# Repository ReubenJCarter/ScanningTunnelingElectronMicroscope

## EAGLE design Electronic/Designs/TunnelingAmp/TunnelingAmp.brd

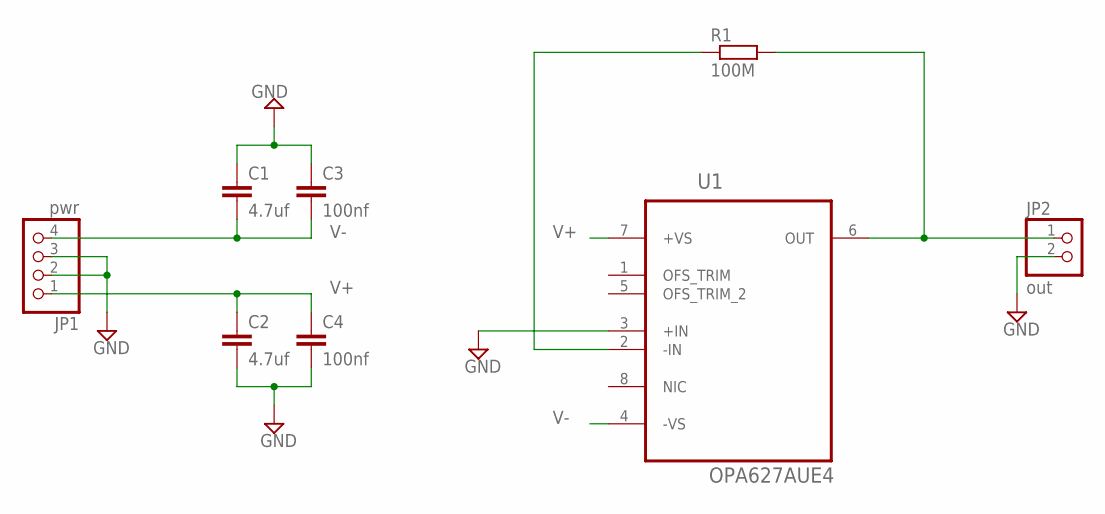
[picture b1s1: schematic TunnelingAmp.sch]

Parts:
C1, C2: 4.7uf; C1210
C3, C4: 100nf; C0603
JP1: pwr; 1X04
JP2: out; 1X02
R1: 100M; R0805
U1: OPA627AUE4; SOIC127P600X175-8N

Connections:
GND: C1.1, C2.2, C3.1, C4.2, JP1.2, JP1.3, JP2.2, U1.3 (+IN)
unnamed: R1.1, U1.2 (-IN)
unnamed: JP2.1, R1.2, U1.6 (OUT)
V+: C2.1, C4.1, JP1.1, U1.7 (+VS)
V-: C1.2, C3.2, JP1.4, U1.4 (-VS)

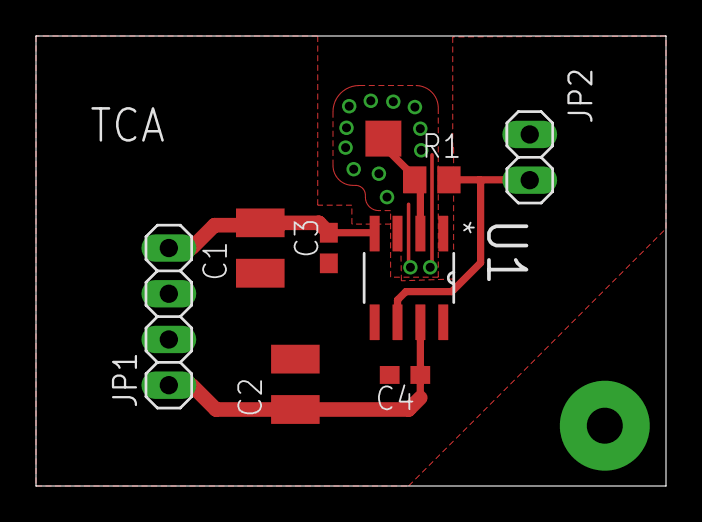
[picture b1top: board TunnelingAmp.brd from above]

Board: 2 copper layers, 35.0 x 25.0 mm, 8 parts (0 on the bottom side), 5 nets.

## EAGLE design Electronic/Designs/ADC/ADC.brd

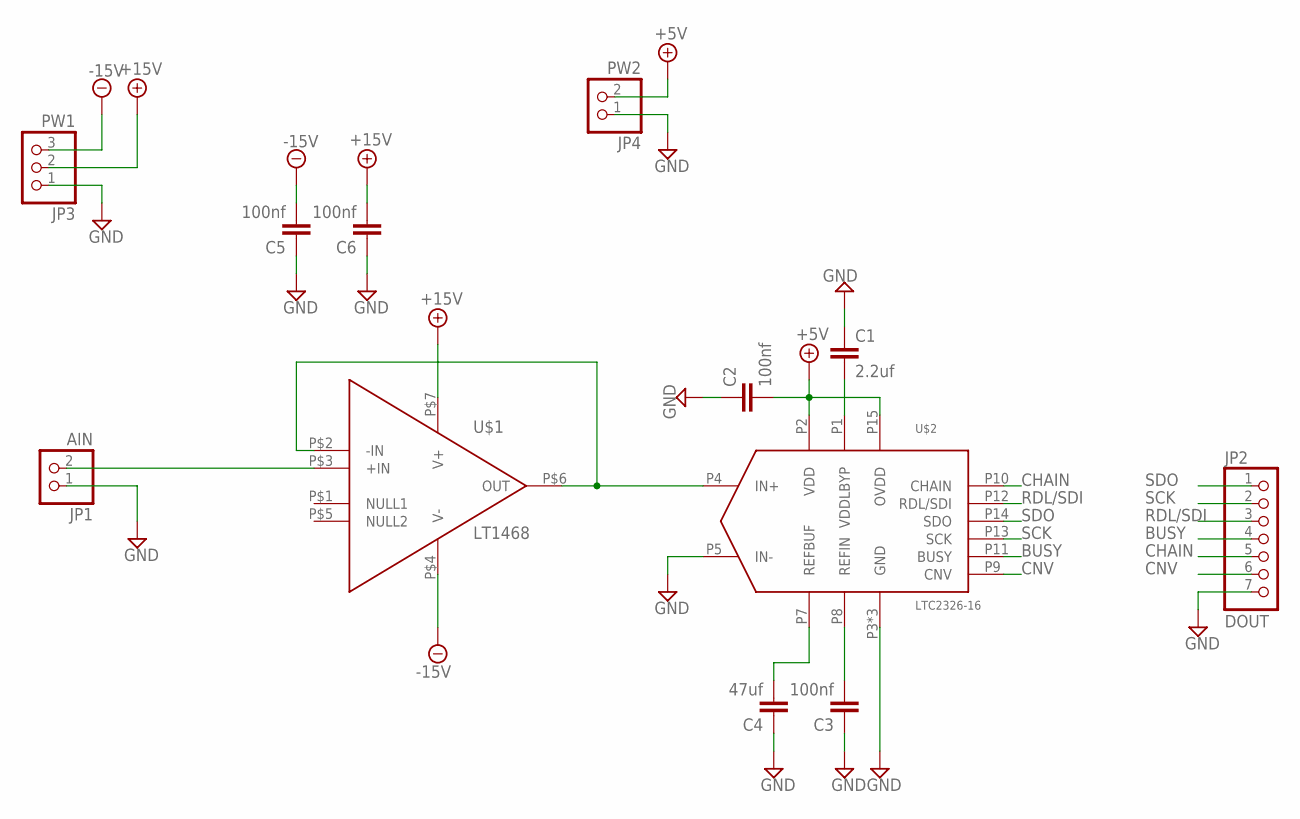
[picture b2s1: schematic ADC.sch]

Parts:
C1: 2.2uf; C0603
C2, C3, C5, C6: 100nf; C0603
C4: 47uf; C0603
JP1: AIN; 1X02
JP2: DOUT; 1X07
JP3: PW1; 1X03
JP4: PW2; 1X02
U$1: LT1468; SOIC-8
U$2: LTC2326-16; 16-MSOP

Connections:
+5V: C2.2, JP4.2, U$2.P2 (VDD), U$2.P15 (OVDD)
+15V: C6.2, JP3.2, U$1.P$7 (V+)
-15V: C5.2, JP3.3, U$1.P$4 (V-)
BUSY: JP2.4, U$2.P11 (BUSY)
CHAIN: JP2.5, U$2.P10 (CHAIN)
CNV: JP2.6, U$2.P9 (CNV)
GND: C1.1, C2.1, C3.1, C4.1, C5.1, C6.1, JP1.1, JP2.7, JP3.1, JP4.1, U$2.P3 (GND), U$2.P5 (IN-), U$2.P6 (GND), U$2.P16 (GND)
unnamed: U$1.P$2 (-IN), U$1.P$6 (OUT), U$2.P4 (IN+)
unnamed: C4.2, U$2.P7 (REFBUF)
unnamed: C3.2, U$2.P8 (REFIN)
unnamed: C1.2, U$2.P1 (VDDLBYP)
unnamed: JP1.2, U$1.P$3 (+IN)
RDL/SDI: JP2.3, U$2.P12 (RDL/SDI)
SCK: JP2.2, U$2.P13 (SCK)
SDO: JP2.1, U$2.P14 (SDO)

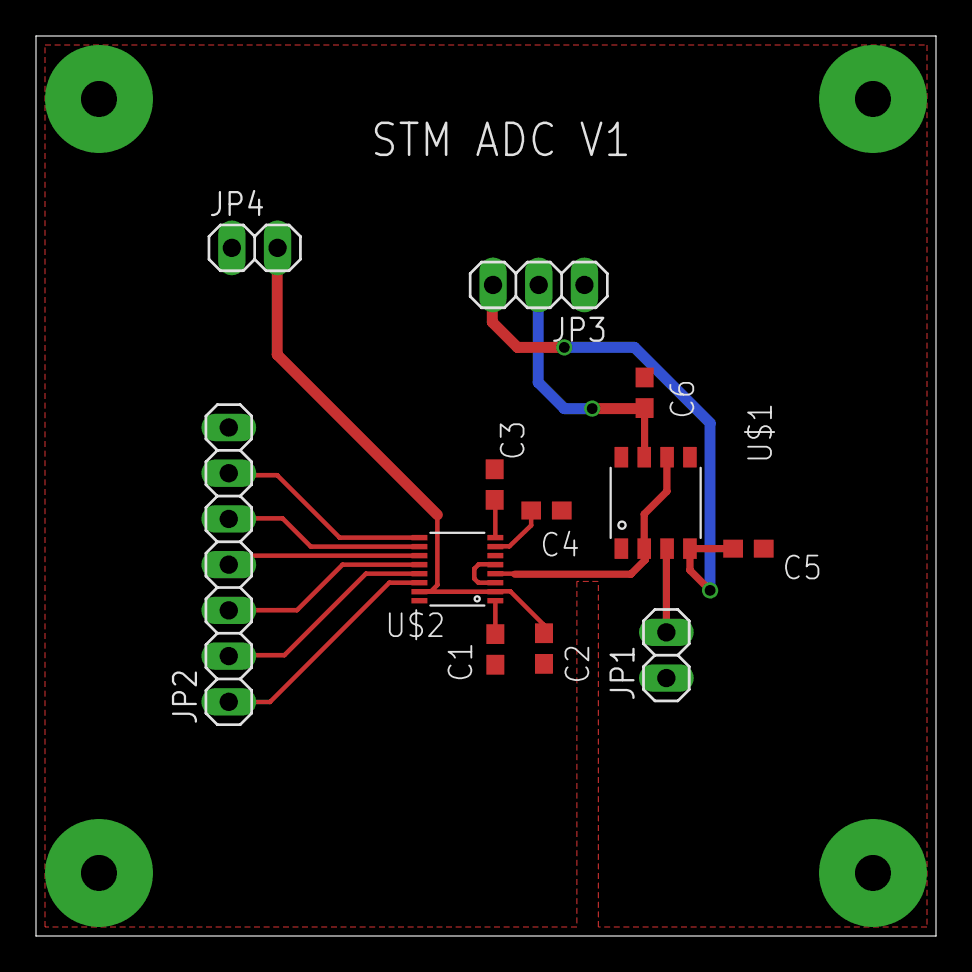
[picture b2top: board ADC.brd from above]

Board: 2 copper layers, 50.0 x 50.0 mm, 12 parts (0 on the bottom side), 15 nets.

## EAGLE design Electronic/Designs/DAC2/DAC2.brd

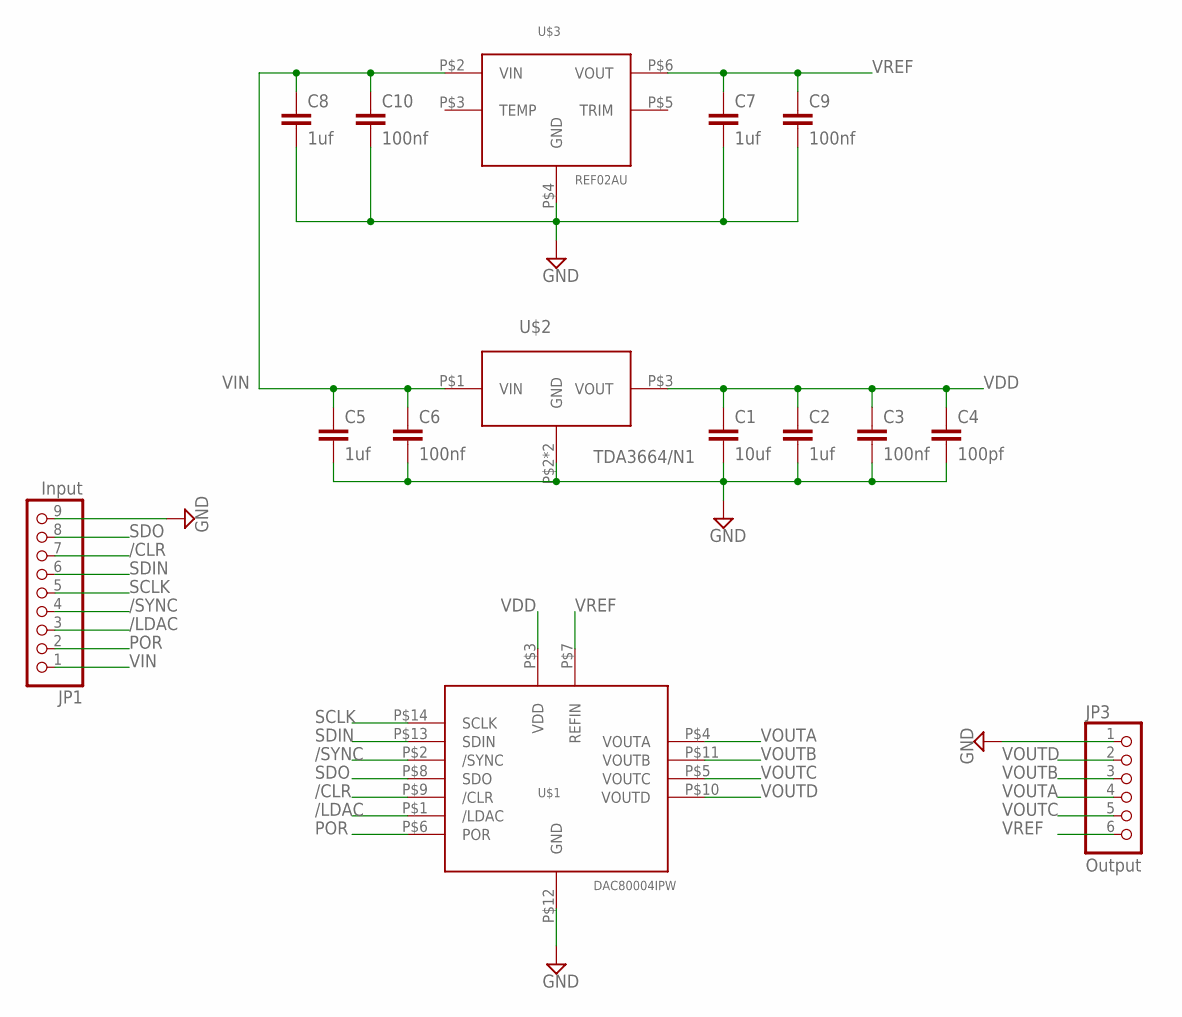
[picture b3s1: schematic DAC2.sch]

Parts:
C1: 10uf; C1210
C2, C5, C7, C8: 1uf; C0603
C3, C6, C9, C10: 100nf; C0603
C4: 100pf; C0603
JP1: Input; 1X09
JP3: Output; 1X06
U$1: DAC80004IPW; TSSOP14
U$2: TDA3664/N1; SOT223
U$3: REF02AU; SO8

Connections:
/CLR: JP1.7, U$1.P$9 (/CLR)
/LDAC: JP1.3, U$1.P$1 (/LDAC)
/SYNC: JP1.4, U$1.P$2 (/SYNC)
GND: C1.2, C2.2, C3.2, C4.2, C5.2, C6.2, C7.2, C8.2, C9.2, C10.2, JP1.9, JP3.1, U$1.P$12 (GND), U$2.P$2 (GND), U$2.P$4 (GND), U$3.P$4 (GND)
POR: JP1.2, U$1.P$6 (POR)
SCLK: JP1.5, U$1.P$14 (SCLK)
SDIN: JP1.6, U$1.P$13 (SDIN)
SDO: JP1.8, U$1.P$8 (SDO)
VDD: C1.1, C2.1, C3.1, C4.1, U$1.P$3 (VDD), U$2.P$3 (VOUT)
VIN: C5.1, C6.1, C8.1, C10.1, JP1.1, U$2.P$1 (VIN), U$3.P$2 (VIN)
VOUTA: JP3.4, U$1.P$4 (VOUTA)
VOUTB: JP3.3, U$1.P$11 (VOUTB)
VOUTC: JP3.5, U$1.P$5 (VOUTC)
VOUTD: JP3.2, U$1.P$10 (VOUTD)
VREF: C7.1, C9.1, JP3.6, U$1.P$7 (REFIN), U$3.P$6 (VOUT)

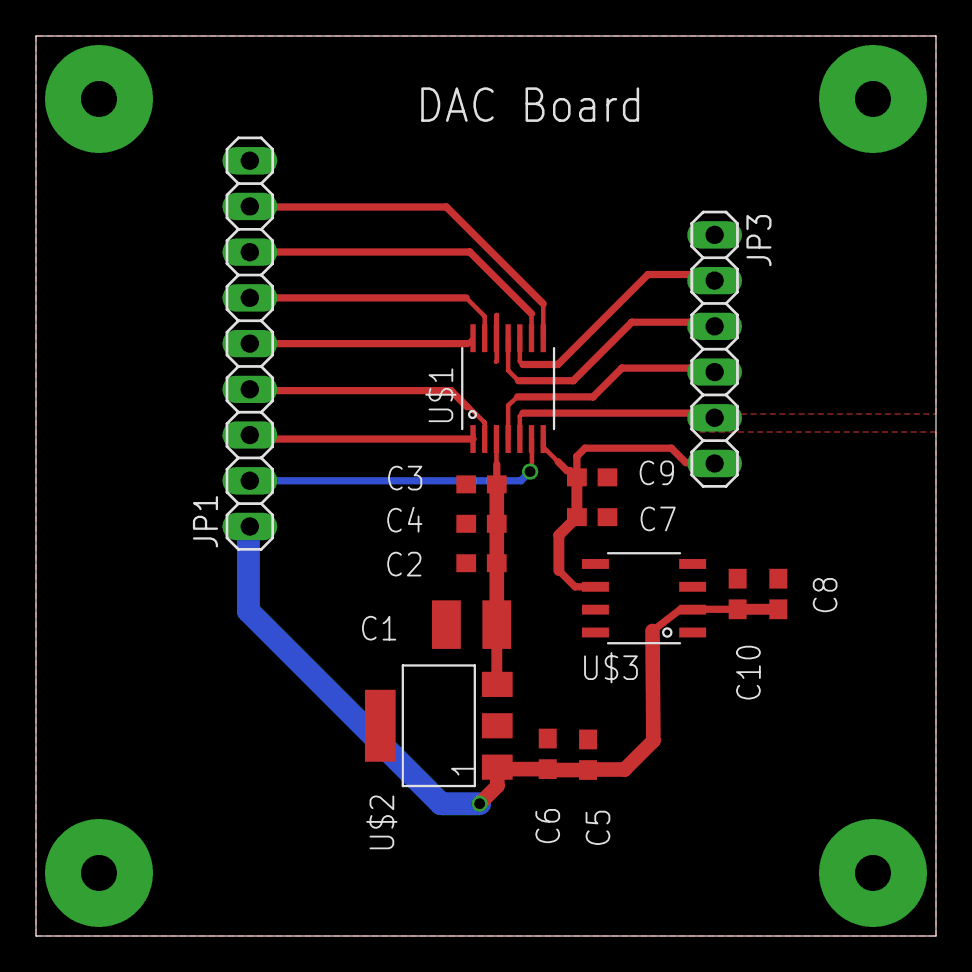
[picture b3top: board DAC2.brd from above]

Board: 2 copper layers, 50.0 x 50.0 mm, 15 parts (0 on the bottom side), 15 nets.

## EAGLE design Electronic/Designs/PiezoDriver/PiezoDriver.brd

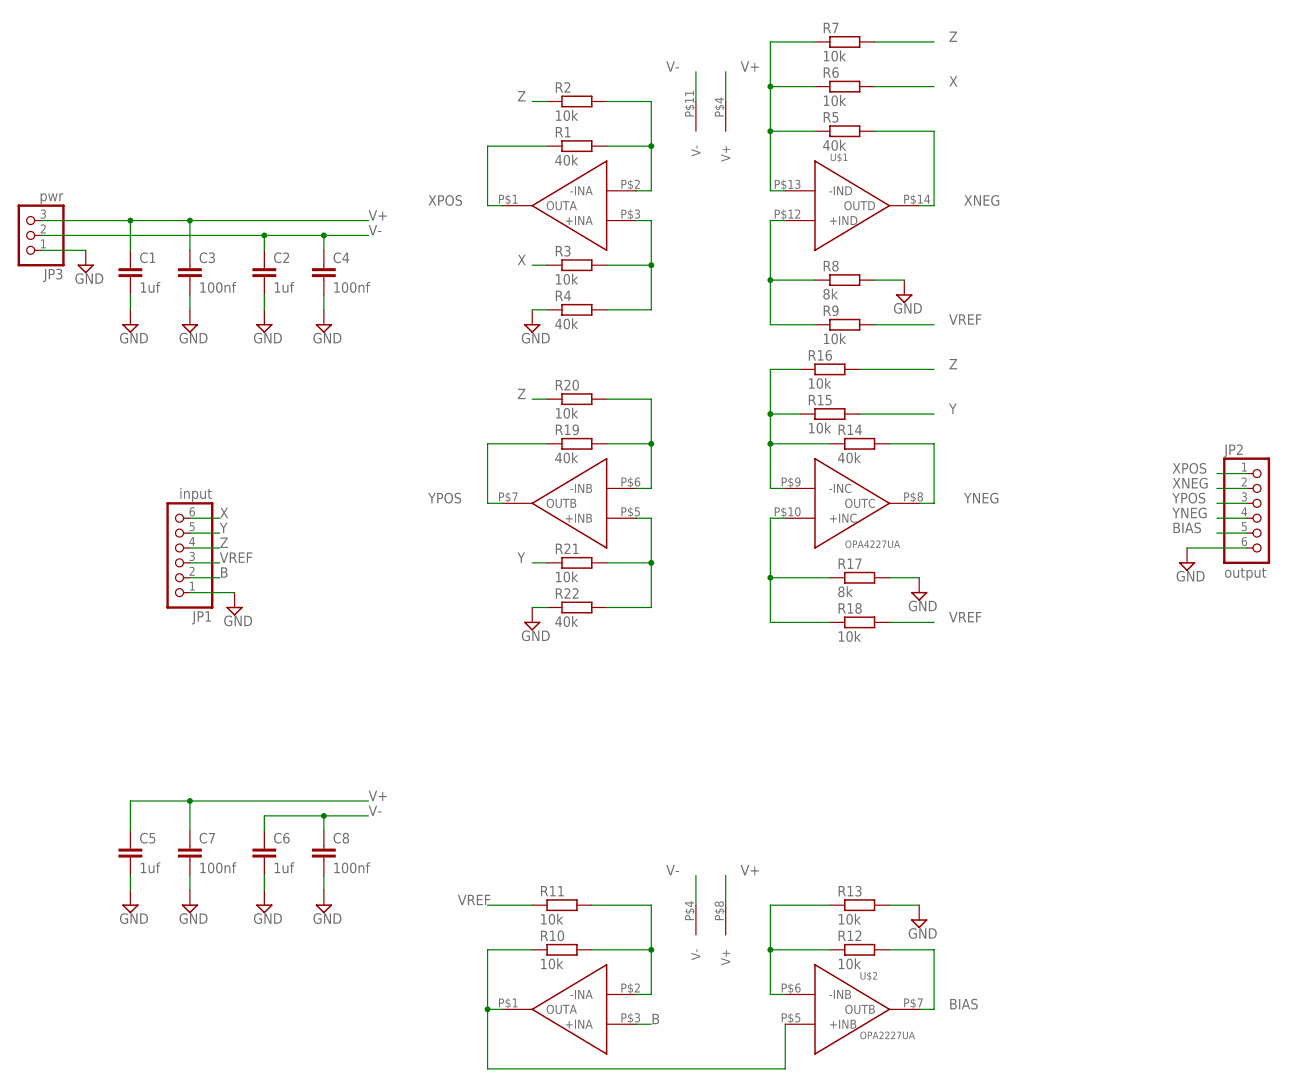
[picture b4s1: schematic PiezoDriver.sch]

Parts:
C1, C2, C5, C6: 1uf; C0603
C3, C4, C7, C8: 100nf; C0603
JP1: input; 1X06
JP2: output; 1X06
JP3: pwr; 1X03
R1, R4, R5, R14, R19, R22: 40k; R0603
R2, R3, R6, R7, R9, R10, R11, R12, R13, R15, R16, R18, R20, R21: 10k; R0603
R8, R17: 8k; R0603
U$1: OPA4227UA; SOIC-14
U$2: OPA2227UA; SOIC-8

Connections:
B: JP1.2, U$2.P$3 (+INA)
BIAS: JP2.5, R12.2, U$2.P$7 (OUTB)
GND: C1.2, C2.2, C3.2, C4.2, C5.2, C6.2, C7.2, C8.2, JP1.1, JP2.6, JP3.1, R4.1, R8.2, R13.2, R17.2, R22.1
unnamed: R1.2, R2.2, U$1.P$2 (-INA)
unnamed: R19.2, R20.2, U$1.P$6 (-INB)
unnamed: R3.2, R4.2, U$1.P$3 (+INA)
unnamed: R14.1, R15.1, R16.1, U$1.P$9 (-INC)
unnamed: R5.1, R6.1, R7.1, U$1.P$13 (-IND)
unnamed: R8.1, R9.1, U$1.P$12 (+IND)
unnamed: R10.1, U$2.P$1 (OUTA), U$2.P$5 (+INB)
unnamed: R10.2, R11.2, U$2.P$2 (-INA)
unnamed: R12.1, R13.1, U$2.P$6 (-INB)
unnamed: R17.1, R18.1, U$1.P$10 (+INC)
unnamed: R21.2, R22.2, U$1.P$5 (+INB)
V+: C1.1, C3.1, C5.1, C7.1, JP3.3, U$1.P$4 (V+), U$2.P$8 (V+)
V-: C2.1, C4.1, C6.1, C8.1, JP3.2, U$1.P$11 (V-), U$2.P$4 (V-)
VREF: JP1.3, R9.2, R11.1, R18.2
X: JP1.6, R3.1, R6.2
XNEG: JP2.2, R5.2, U$1.P$14 (OUTD)
XPOS: JP2.1, R1.1, U$1.P$1 (OUTA)
Y: JP1.5, R15.2, R21.1
YNEG: JP2.4, R14.2, U$1.P$8 (OUTC)
YPOS: JP2.3, R19.1, U$1.P$7 (OUTB)
Z: JP1.4, R2.1, R7.2, R16.2, R20.1

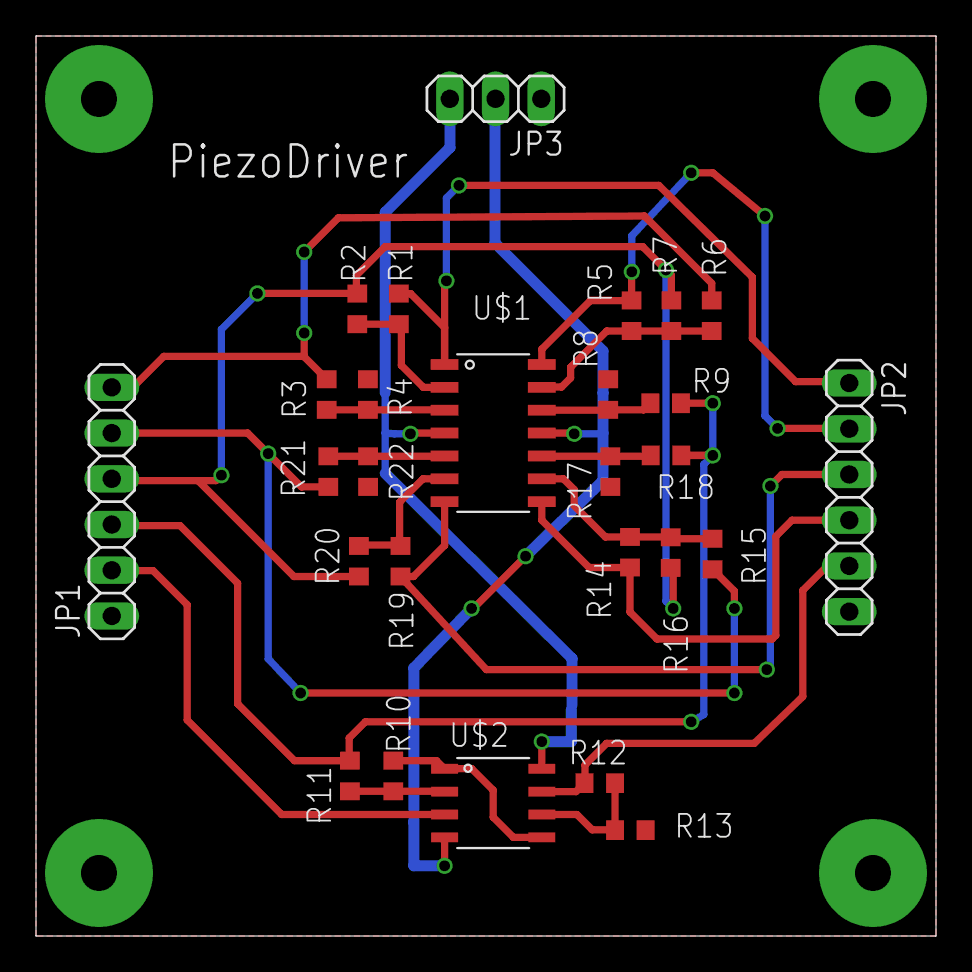
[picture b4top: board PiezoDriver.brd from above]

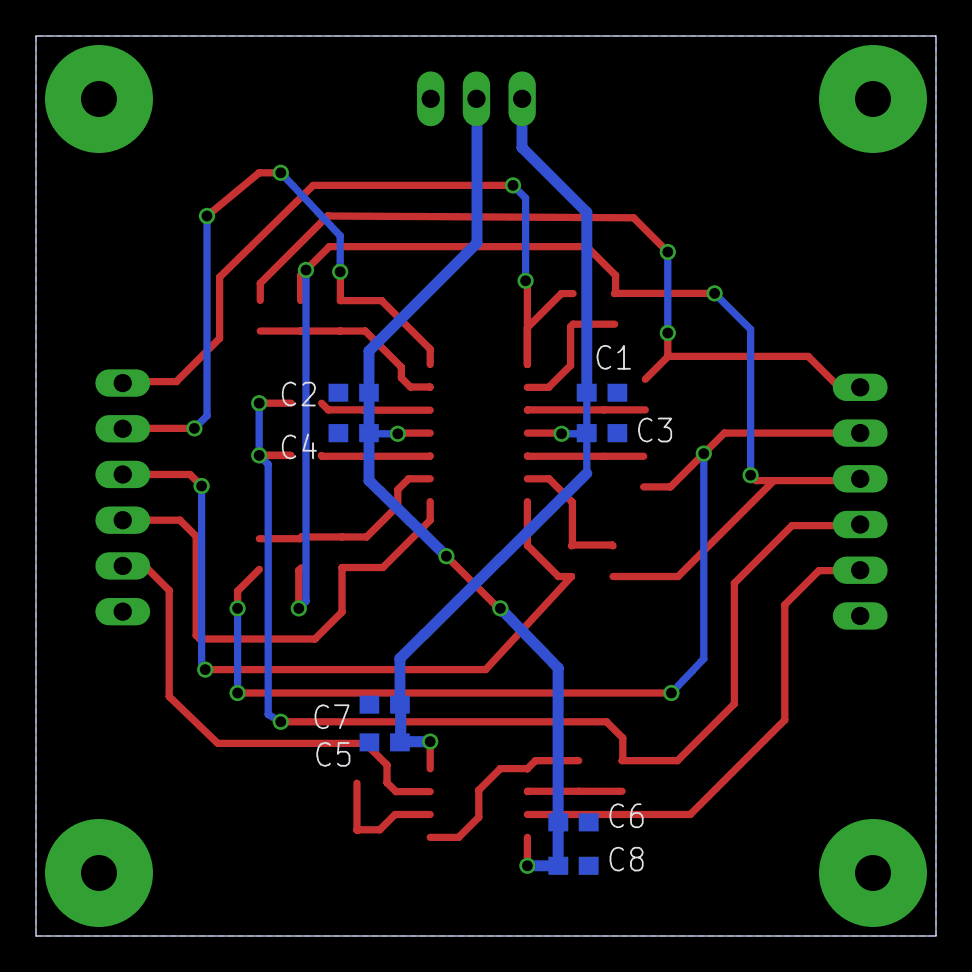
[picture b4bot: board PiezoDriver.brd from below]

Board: 2 copper layers, 50.0 x 50.0 mm, 35 parts (8 on the bottom side), 24 nets.

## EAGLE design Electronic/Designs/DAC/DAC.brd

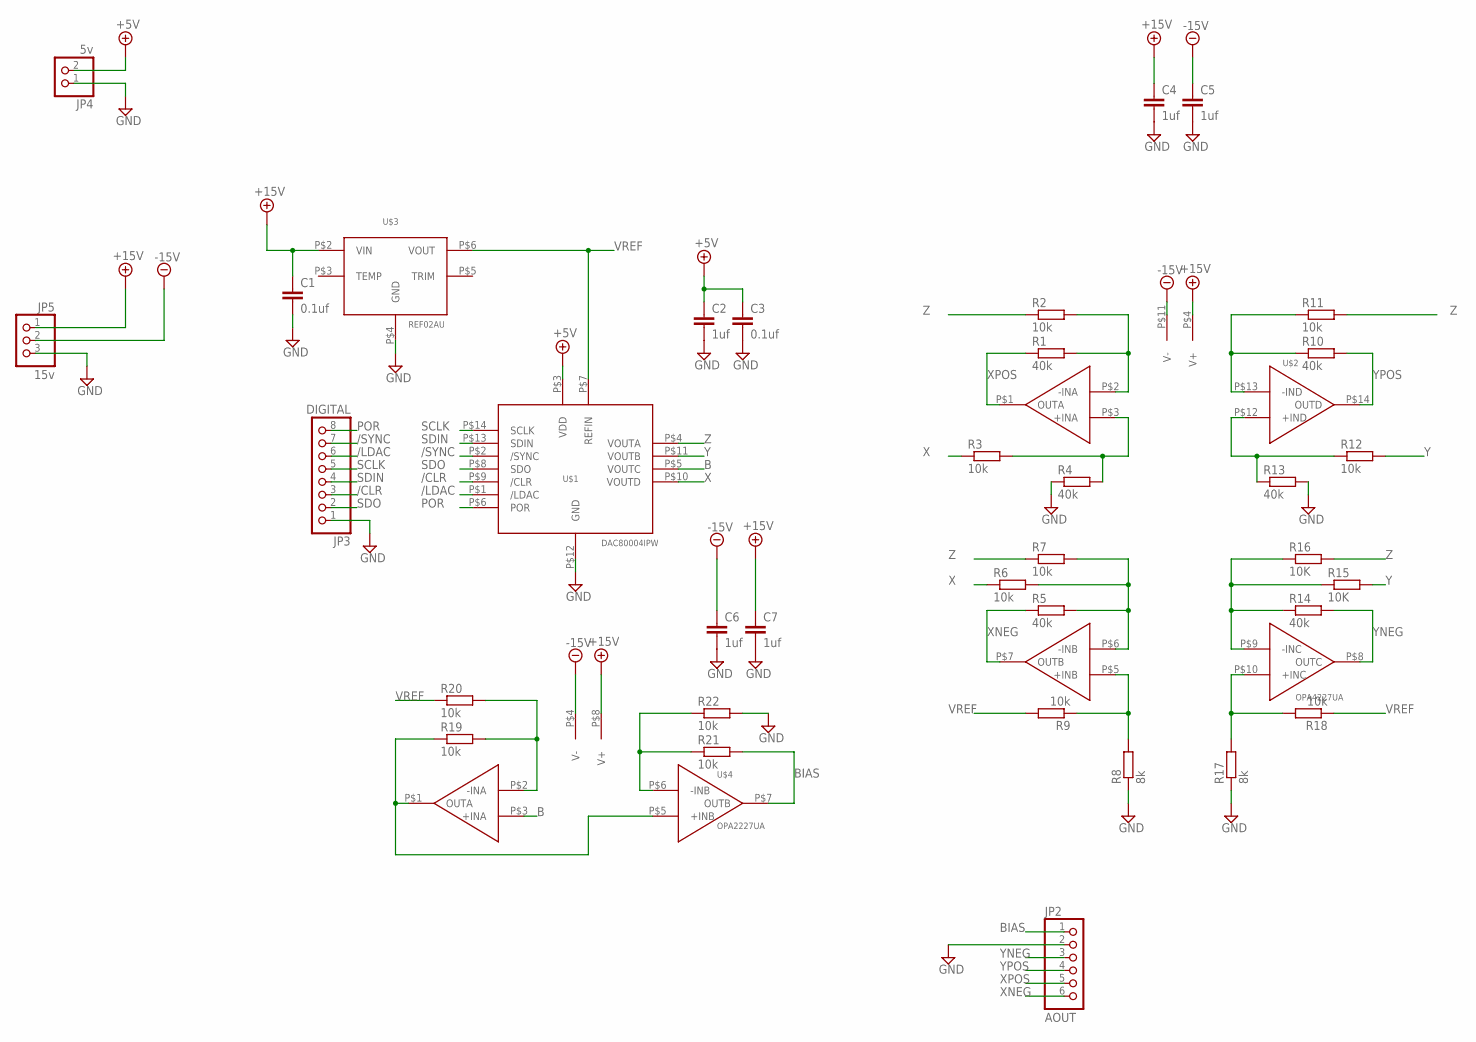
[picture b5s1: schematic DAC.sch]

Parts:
C1, C3: 0.1uf; C0603
C2, C4, C5, C6, C7: 1uf; C0603
JP2: AOUT; 1X06
JP3: DIGITAL; 1X08
JP4: 5v; 1X02
JP5: 15v; 1X03
R1, R4, R5, R10, R13, R14: 40k; R0603
R2, R3, R6, R7, R9, R11, R12, R18, R19, R20, R21, R22: 10k; R0603
R8, R17: 8k; R0603
R15, R16: 10K; R0603
U$1: DAC80004IPW; TSSOP14
U$2: OPA4227UA; SOIC-14
U$3: REF02AU; SO8
U$4: OPA2227UA; SOIC-8

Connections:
+5V: C2.1, C3.1, JP4.2, U$1.P$3 (VDD)
+15V: C1.1, C4.1, C7.1, JP5.1, U$2.P$4 (V+), U$3.P$2 (VIN), U$4.P$8 (V+)
-15V: C5.1, C6.1, JP5.2, U$2.P$11 (V-), U$4.P$4 (V-)
/CLR: JP3.3, U$1.P$9 (/CLR)
/LDAC: JP3.6, U$1.P$1 (/LDAC)
/SYNC: JP3.7, U$1.P$2 (/SYNC)
B: U$1.P$5 (VOUTC), U$4.P$3 (+INA)
BIAS: JP2.1, R21.2, U$4.P$7 (OUTB)
GND: C1.2, C2.2, C3.2, C4.2, C5.2, C6.2, C7.2, JP2.2, JP3.1, JP4.1, JP5.3, R4.1, R8.1, R13.2, R17.1, R22.2, U$1.P$12 (GND), U$3.P$4 (GND)
unnamed: R1.2, R2.2, U$2.P$2 (-INA)
unnamed: R3.2, R4.2, U$2.P$3 (+INA)
unnamed: R5.2, R6.2, R7.2, U$2.P$6 (-INB)
unnamed: R8.2, R9.1, U$2.P$5 (+INB)
unnamed: R12.1, R13.1, U$2.P$12 (+IND)
unnamed: R14.1, R15.1, R16.1, U$2.P$9 (-INC)
unnamed: R10.1, R11.1, U$2.P$13 (-IND)
unnamed: R19.2, R20.2, U$4.P$2 (-INA)
unnamed: R17.2, R18.2, U$2.P$10 (+INC)
unnamed: R19.1, U$4.P$1 (OUTA), U$4.P$5 (+INB)
unnamed: R21.1, R22.1, U$4.P$6 (-INB)
POR: JP3.8, U$1.P$6 (POR)
SCLK: JP3.5, U$1.P$14 (SCLK)
SDIN: JP3.4, U$1.P$13 (SDIN)
SDO: JP3.2, U$1.P$8 (SDO)
VREF: R9.2, R18.1, R20.1, U$1.P$7 (REFIN), U$3.P$6 (VOUT)
X: R3.1, R6.1, U$1.P$10 (VOUTD)
XNEG: JP2.6, R5.1, U$2.P$7 (OUTB)
XPOS: JP2.5, R1.1, U$2.P$1 (OUTA)
Y: R12.2, R15.2, U$1.P$11 (VOUTB)
YNEG: JP2.3, R14.2, U$2.P$8 (OUTC)
YPOS: JP2.4, R10.2, U$2.P$14 (OUTD)
Z: R2.1, R7.1, R11.2, R16.2, U$1.P$4 (VOUTA)

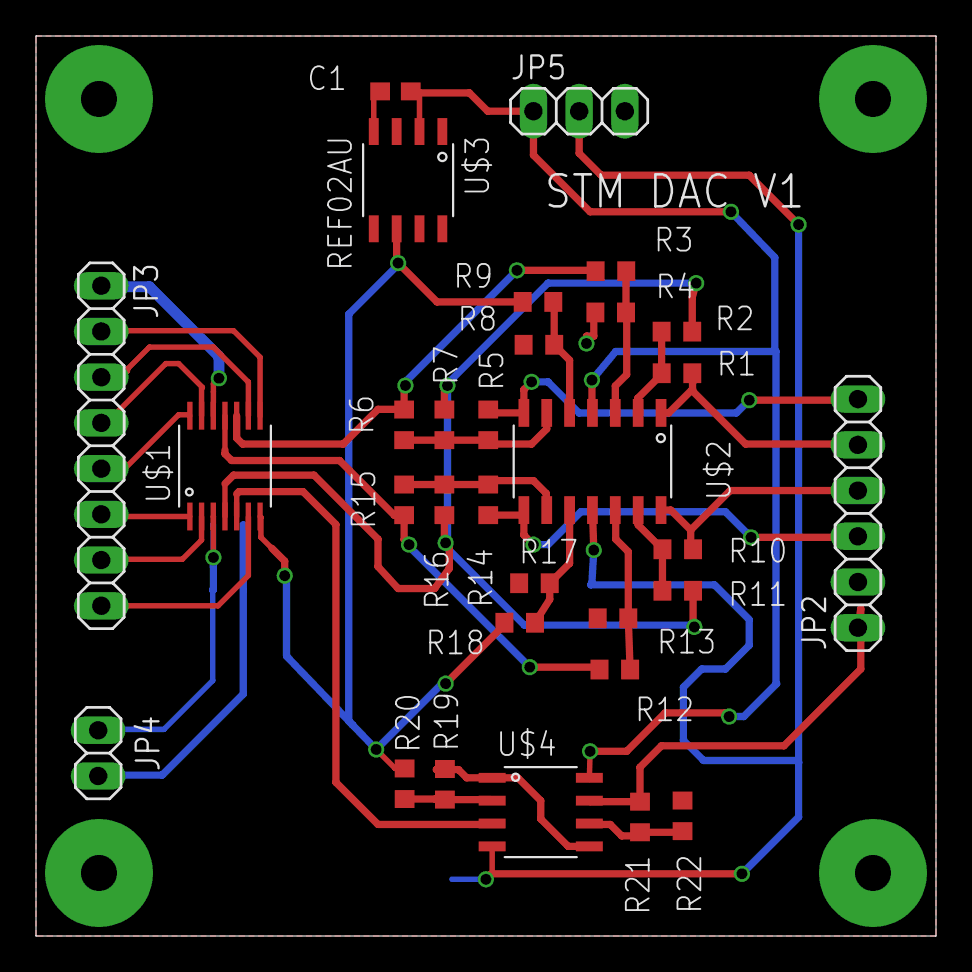
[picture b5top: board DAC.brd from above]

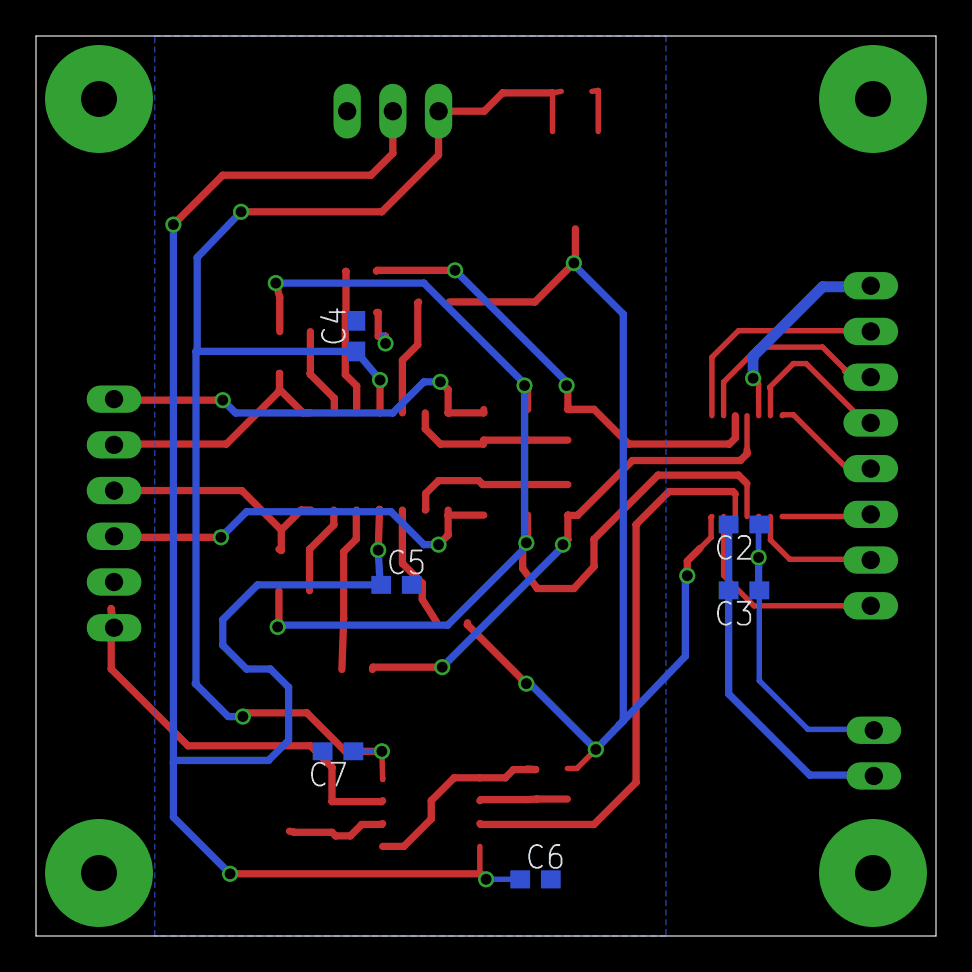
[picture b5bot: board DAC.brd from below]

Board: 2 copper layers, 50.0 x 50.0 mm, 37 parts (6 on the bottom side), 32 nets.

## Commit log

2017-02-16 Added Everything so far (Mostly structure, but also DAC board so far)
2017-02-16 added OPA2227 to OPAx22x library
2017-02-18 Moved around into Electronic folder
2017-02-18 Added PSU folder
2017-02-18 added tunneing current amplifier Simulation
2017-02-18 added to the adc and adc opamp lib
2017-02-27 added new part to dac board
2017-02-27 Added ADC board and schematic
2017-02-28 adjusted adc pwr pins on board
2017-02-28 added itead drc and cam files
2017-03-02 split power pins from 5v and 15v
2017-03-03 added to dac pcb
2017-03-07 Added to DAC board file
2017-03-07 improved dac board layout
2017-03-08 Added to dac pcb finished routing
2017-03-09 Added Mains powersupply to simulation of power supply
2017-03-10 increassed isolation distance to 12MIL on DAC board, this breaks alot of ground connections
2017-03-10 Added to PSU inductor transformer
2017-03-11 Increassed isolation for ADC board, fixed DAC board isolation errors, and added mounting holes for ADC board
2017-03-11 added mounting holes to dac board
2017-03-11 added dirt cheap drc / cam files , minor fix to board dac
2017-04-20 reduced path of analogue signal from opamp to adc
2017-04-20 fixed floating air wire
2017-04-20 Added board names
2017-04-20 modified eagle cad cam file from exelleron to exelleron24 drill cam
2017-04-20 Fixed CAM file drill offset problem and fixed overlaps of silkscreen on DAC board
2017-05-27 Added dac board 2
2017-06-17 Added new piezoDrive and holes for DAC2 and new lib OPA627
2017-06-18 Added Tunneling Current Amp Sch OPA627 from farnell
2017-06-18 Added tunneling current board
2017-06-18 Added guard ring to tunneling current amp
2017-06-21 Added to tunneling amp
2017-06-22 Added Guard ring to Tunneling amp
2017-06-24 added tstop to guard
2017-06-24 Added piezo driver
2017-06-27 Added to Piezo Driver Board
2017-07-03 Added to piezo board
2017-07-06 Added to piezo driver
2017-07-09 added application first code
2017-07-10 Added To GUI for STM Application
2017-07-16 added grid layout to control panel
2017-07-16 added graphics view for scanimage to application
2017-07-16 set style back to dark
2017-07-26 Added better Cmake QT Find and added dac2 piezo and tun boards
2017-08-07 added change to DAC2 board
2017-08-30 Added Thicker traces to power on PCB of tun amp
2017-10-06 moved silkscreen text in ADC
2018-02-18 Added firmware software project so far
2018-02-20 Added pin mode setup for firmware
2018-02-20 added to DAC driver
2018-02-22 Added PID controller and added to DAC driver in firmware
2018-02-22 added to timings for dac driver
2018-02-24 added adc driver code
2018-03-03 Added to the DAC driver firmware
2018-03-05 Added to the firmware
2018-03-06 Added to firmware
2018-03-07 added to pc software
2018-03-07 Added hardware interface to pc software
2018-03-12 Added console and Device connection panels to software
